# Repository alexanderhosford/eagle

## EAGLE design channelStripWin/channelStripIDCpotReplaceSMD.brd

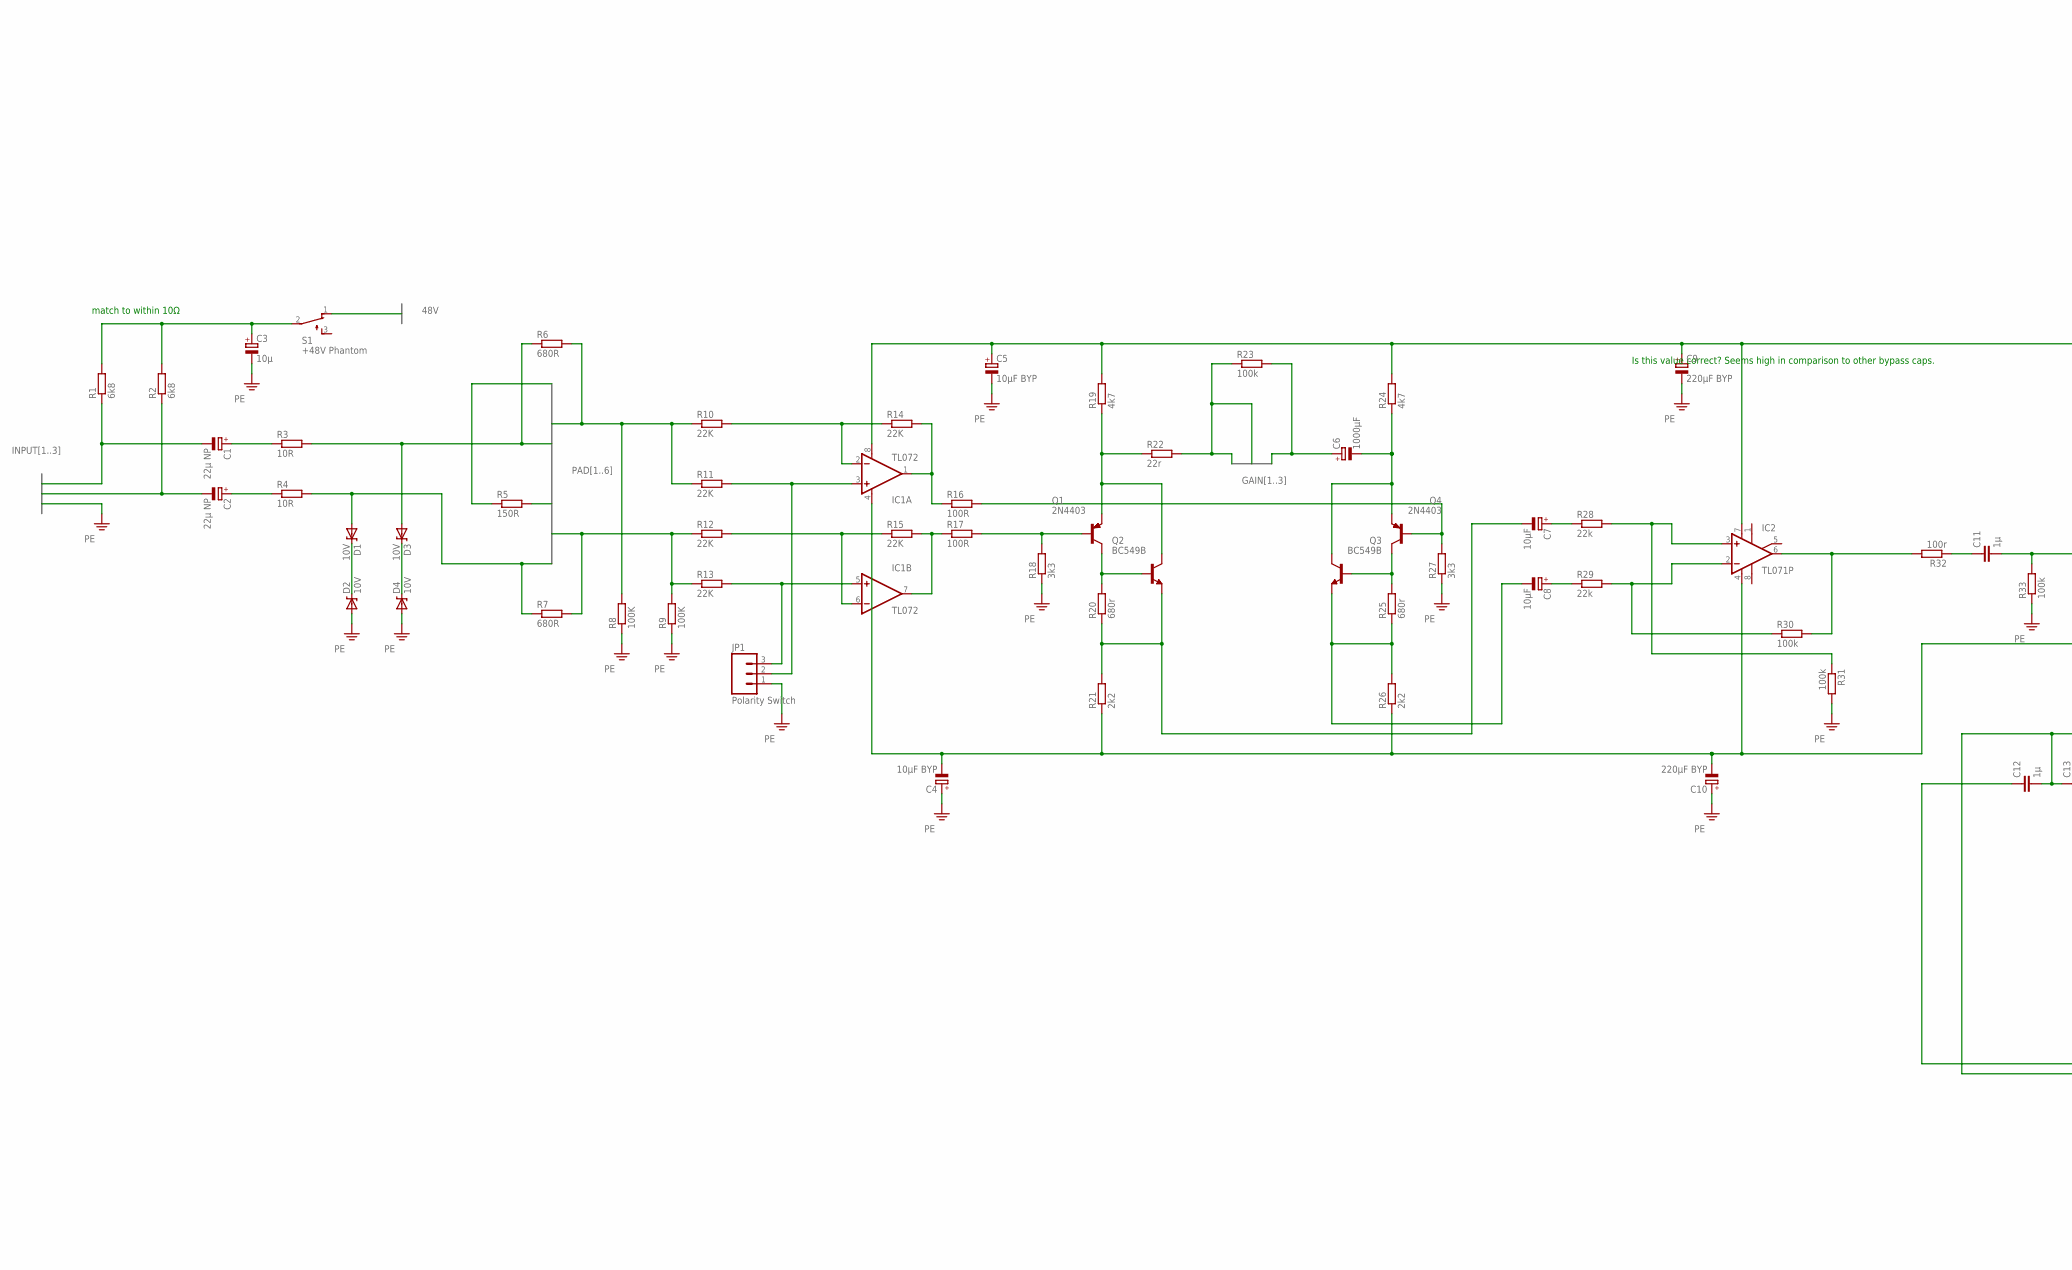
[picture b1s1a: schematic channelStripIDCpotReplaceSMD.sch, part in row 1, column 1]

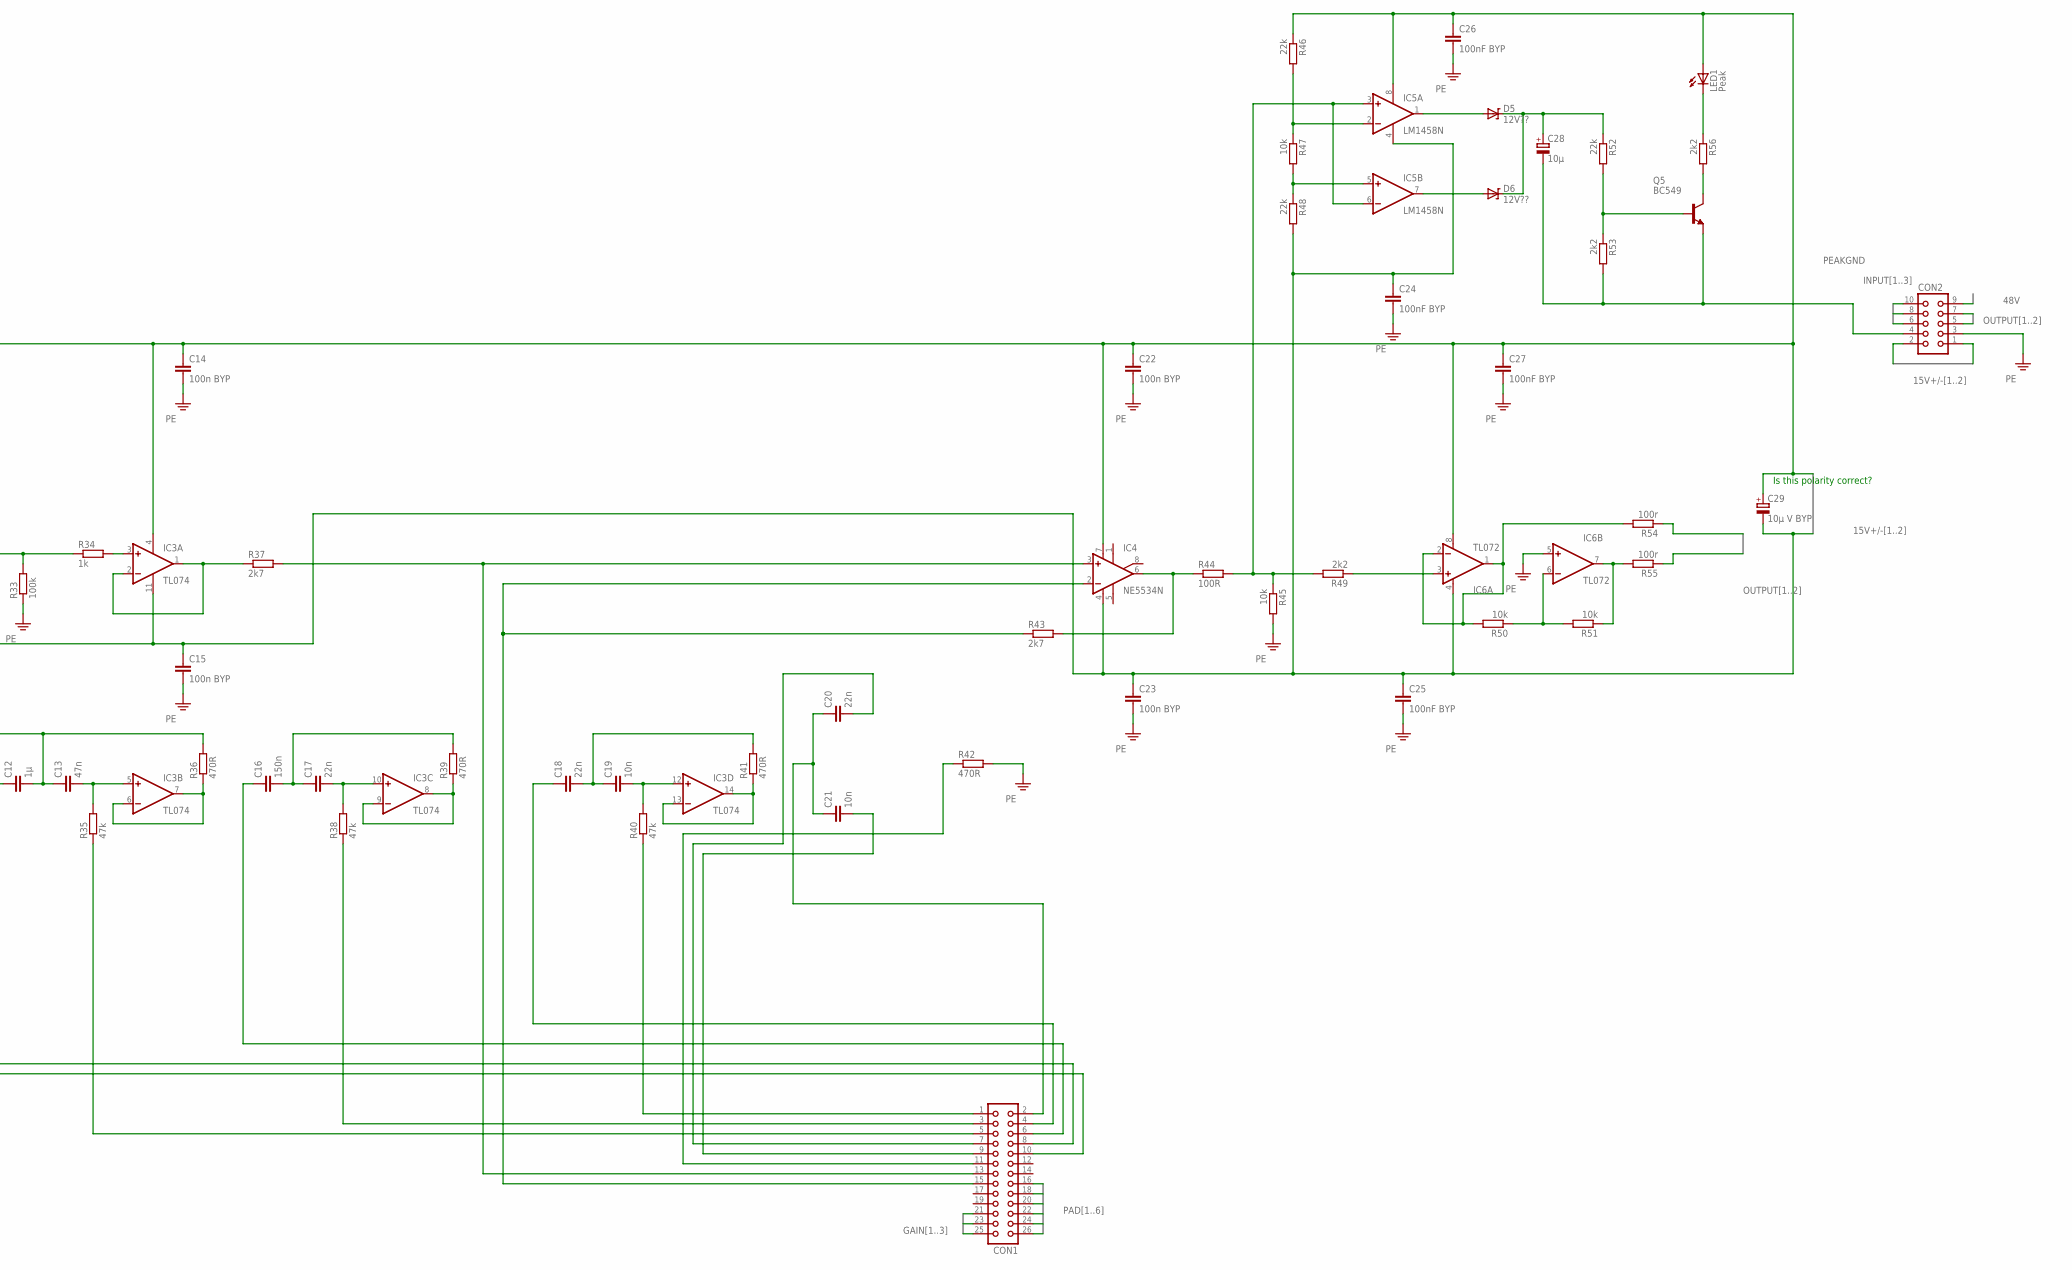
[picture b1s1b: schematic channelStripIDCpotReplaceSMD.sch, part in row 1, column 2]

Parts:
C1, C2: 22µ NP; E2,5-5
C3: 10µ; E2,5-6
C4, C5: 10µF BYP; E2,5-6
C6: 1000µF; E5-10,5
C7, C8: 10µF; E15-5
C9, C10: 220µF BYP; E5-10,5
C11, C12: 1µ; C050-025X075
C13: 47n; C050-025X075
C14, C15, C22, C23: 100n BYP; C050-025X075
C16: 150n; C050-025X075
C17, C18, C20: 22n; C050-025X075
C19, C21: 10n; C050-025X075
C24, C25, C26, C27: 100nF BYP; C050-025X075
C28: 10µ; E2,5-6E
C29: 10µ V BYP; E2,5-6E
CON1: CON26
CON2: CON10
D1, D2, D3, D4: 10V; DIODE-ZENER
D5, D6: 12V??; DIODE-ZENER
IC1, IC6: TL072; DIP08
IC2: TL071P; DIL08
IC3: TL074; DIL14
IC4: NE5534N; DIL08
IC5: LM1458N; DIL08
JP1: Polarity Switch; 1X03
LED1: Peak; LED3MM-NS
Q1, Q4: 2N4403; TO92-BCE
Q2, Q3: BC549B; TO92-EBC
Q5: BC549; TO92-EBC
R1, R2: 6k8; M1206
R3, R4: 10R; M1206
R5: 150R; M1206
R6, R7: 680R; M1206
R8, R9: 100K; M1206
R10, R11, R12, R13, R14, R15: 22K; M1206
R16, R17, R44: 100R; M1206
R18, R27: 3k3; M1206
R19, R24: 4k7; M1206
R20, R25: 680r; M1206
R21, R26, R49, R53, R56: 2k2; M1206
R22: 22r; M1206
R23, R30, R31, R33: 100k; M1206
R28, R29, R46, R48, R52: 22k; M1206
R32, R54, R55: 100r; M1206
R34: 1k; M1206
R35, R38, R40: 47k; M1206
R36, R39, R41, R42: 470R; M1206
R37, R43: 2k7; M1206
R45, R47, R50, R51: 10k; M1206
S1: +48V Phantom; TL3XPO

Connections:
15V+/-1: C4.-, C10.-, C15.1, C23.1, C24.1, C25.1, C29.-, CON2.1, IC1.4 (V-), IC2.4 (V-), IC3.11 (V-), IC4.4 (V-), IC5.4 (V-), IC6.4 (V-), R21.1, R26.1, R48.2
15V+/-2: C5.+, C9.+, C14.1, C22.1, C26.1, C27.1, C29.+, CON2.2, IC1.8 (V+), IC2.7 (V+), IC3.4 (V+), IC4.7 (V+), IC5.8 (V+), IC6.8 (V+), LED1.A, R19.2, R24.2, R46.1
48V: CON2.9, S1.1 (O)
GAIN1: C6.+, CON1.21, R23.2
GAIN2: CON1.23, CON1.25, R22.2, R23.1
GND: C3.-, C4.+, C5.-, C9.-, C10.+, C14.2, C15.2, C22.2, C23.2, C24.2, C25.2, C26.2, C27.2, D2.P$2 (A), D4.P$2 (A), IC6.5 (+IN), JP1.1, R8.1, R9.1, R18.1, R27.1, R31.2, R33.1, R42.2, R45.2
INPUT1: C1.-, CON2.10, R1.1
INPUT2: C2.-, CON2.8, R2.1
INPUT3: CON2.6
unnamed: C18.1, CON1.4
unnamed: IC6.7 (OUT), R51.1, R55.2
unnamed: C7.-, Q2.E, R20.1, R21.2
unnamed: C16.2, C17.1, R39.2
unnamed: C18.2, C19.1, R41.2
unnamed: C21.2, CON1.9
unnamed: C20.2, CON1.7
unnamed: CON1.11, R42.1
unnamed: IC3.13 (-IN), IC3.14 (OUT), R41.1
unnamed: C19.2, IC3.12 (+IN), R40.2
unnamed: CON1.3, R38.1
unnamed: C11.1, R32.1
unnamed: C11.2, R33.2, R34.1
unnamed: IC3.3 (+IN), R34.2
unnamed: IC3.1 (OUT), IC3.2 (-IN), R37.1
unnamed: CON1.15, IC4.2 (-IN), R43.1
unnamed: IC4.6 (OUT), R43.2, R44.1
unnamed: Q5.B, R52.2, R53.1
unnamed: C1.+, R3.1
unnamed: IC3.6 (-IN), IC3.7 (OUT), R36.1
unnamed: C13.2, IC3.5 (+IN), R35.2
unnamed: CON1.5, R35.1
unnamed: C12.1, CON1.8
unnamed: IC3.8 (OUT), IC3.9 (-IN), R39.1
unnamed: C2.+, R4.1
unnamed: C17.2, IC3.10 (+IN), R38.2
unnamed: CON1.1, R40.1
unnamed: IC5.2 (-IN), R46.2, R47.1
unnamed: C3.+, R1.2, R2.2, S1.2
unnamed: IC2.3 (+IN), R28.2, R31.1
unnamed: IC6.6 (-IN), R50.1, R51.2
unnamed: IC6.1 (OUT), IC6.2 (-IN), R50.2, R54.2
unnamed: IC6.3 (+IN), R49.1
unnamed: C20.1, C21.1, CON1.2
unnamed: C7.+, R28.1
unnamed: IC2.6 (OUT), R30.2, R32.2
unnamed: IC2.2 (-IN), R29.2, R30.1
unnamed: C8.+, R29.1
unnamed: C6.-, Q3.C, Q4.E, R24.1
unnamed: Q1.E, Q2.C, R19.1, R22.1
unnamed: Q3.B, Q4.C, R25.2
unnamed: IC1.1 (OUT), R14.2, R16.1
unnamed: Q1.C, Q2.B, R20.2
unnamed: IC5.5 (+IN), R47.2, R48.1
unnamed: IC1.7 (OUT), R15.2, R17.1
unnamed: C8.-, Q3.E, R25.1, R26.2
unnamed: Q4.B, R16.2, R27.2
unnamed: Q1.B, R17.2, R18.2
unnamed: IC1.6 (-IN), R12.2, R15.1
unnamed: D3.P$1 (C), D4.P$1 (C)
unnamed: IC1.2 (-IN), R10.2, R14.1
unnamed: IC1.5 (+IN), JP1.3, R13.2
unnamed: IC1.3 (+IN), JP1.2, R11.2
unnamed: D1.P$1 (C), D2.P$1 (C)
unnamed: Q5.C, R56.2
unnamed: C28.+, D5.P$1 (C), D6.P$1 (C), R52.1
unnamed: LED1.K (C), R56.1
unnamed: D5.P$2 (A), IC5.1 (OUT)
unnamed: D6.P$2 (A), IC5.7 (OUT)
unnamed: IC5.3 (+IN), IC5.6 (-IN), R44.2, R45.1, R49.2
unnamed: CON1.13, IC4.3 (+IN), R37.2
unnamed: C16.1, CON1.6
unnamed: C12.2, C13.1, CON1.10, R36.2
OUTPUT1: CON2.5, R55.1
OUTPUT2: CON2.7, R54.1
PAD1: CON1.16, R5.1
PAD2: CON1.18, R6.2, R8.2, R10.1, R11.1
PAD3: CON1.20, D3.P$2 (A), R3.2, R6.1
PAD4: CON1.22, R5.2
PAD5: CON1.24, R7.2, R9.2, R12.1, R13.1
PAD6: CON1.26, D1.P$2 (A), R4.2, R7.1
PE: CON2.3
PEAKGND: C28.-, CON2.4, Q5.E, R53.2

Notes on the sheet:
Is this polarity correct?
Is this value correct? Seems high in comparison to other bypass caps.
match to within 10Ω

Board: 2 copper layers, 107 parts (0 on the bottom side), 80 nets, no tracks yet.

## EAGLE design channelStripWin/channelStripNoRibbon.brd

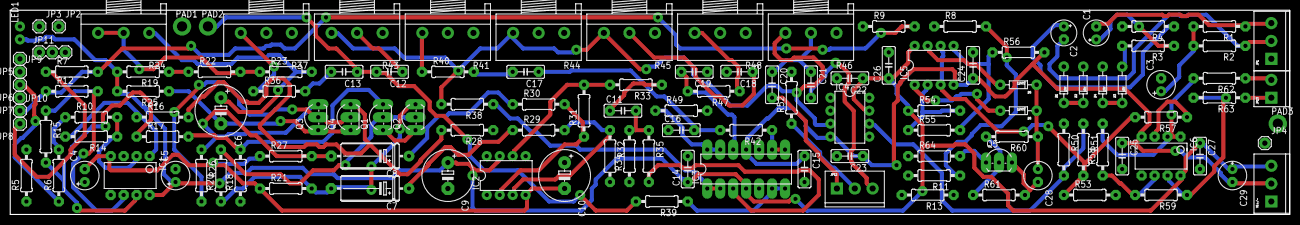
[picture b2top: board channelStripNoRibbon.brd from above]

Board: 2 copper layers, 250.6 x 40.0 mm, 128 parts (0 on the bottom side), 80 nets.

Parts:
C1, C2: 22µ NP; E2,5-5
C3: 10µ; E2,5-6
C4, C5: 10µF BYP; E2,5-6
C6: 1000µF; E5-10,5
C7, C8: 10µF; E15-5
C9, C10: 220µF BYP; E5-10,5
C11, C12: 1µ; C050-025X075
C13: 47n; C050-025X075
C14, C15, C22, C23: 100n BYP; C050-025X075
C16: 150n; C050-025X075
C17, C18, C20: 22n; C050-025X075
C19, C21: 10n; C050-025X075
C24, C25, C26, C27: 100nF BYP; C050-025X075
C28: 10µ; E2,5-6E
C29: 10µ V BYP; E2,5-6E
D1, D2, D3, D4: 10V; DIODE-ZENER
D5, D6: 12V??; DIODE-ZENER
IC1, IC6: TL072; DIP08
IC2: TL071P; DIL08
IC3: TL074; DIL14
IC4: NE5534N; DIL08
IC5: LM1458N; DIL08
JP1: INPUT; SCREWTERMINAL-3.5MM-3
JP2: Phantom On to input; 1X01
JP3: Phantom on to power; 1X01
JP4: +48; 1X01
JP5: 20dB pad L off; 1X01
JP6: 20dB pad L on; 1X01
JP7, JP8: 20dB pad R off; 1X01
JP9: 20dB pad L; 1X01
JP10: 20dB pad R; 1X01
JP11: Polarity Switch; 1X03
JP12: Hi F; SCREWTERMINAL-3.5MM-3
JP13: OUTPUT; SCREWTERMINAL-3.5MM-2
LED1: Peak; LED3MM-NS
PAD1: Shelf/Peak Pin 2; 1X01_2MM
PAD2: Shelf/Peak Pin 1; 1X01_2MM
PAD3: Peak GND; 1X01_2MM
Q1, Q4: 2N4403; TO92-BCE
Q2, Q3: BC549B; TO92-EBC
Q5: BC549; TO92-EBC
R1, R2: 6k8; 0207/10
R3, R4: 10R; 0207/10
R5: 150R; 0207/10
R6, R7: 680R; 0207/10
R8, R9: 100K; 0207/10
R10, R11, R12, R13, R14, R15: 22K; 0207/10
R16, R17, R51: 100R; 0207/10
R18, R28: 3k3; 0207/10
R19, R25: 4k7; 0207/10
R20, R26: 680r; 0207/10
R21, R27, R57, R61, R64: 2k2; 0207/10
R22: 22r; 0207/10
R23, R31, R32, R34: 100k; 0207/10
R24, R43, R44, R45, R46: 10k; 3RP/1610N
R29, R30, R54, R56, R60: 22k; 0207/10
R33, R62, R63: 100r; 0207/10
R35: 1k; 0207/10
R36, R40, R47: 47k; 0207/10
R37, R41, R48: 1M; 3RP/1610N
R38, R50: 2k7; 0207/10
R39, R42, R49, R52: 470R; 0207/10
R53, R55, R58, R59: 10k; 0207/10
VE+/-: POWER; SCREWTERMINAL-3.5MM-3

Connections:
15V+: C5.+, C9.+, C14.1, C22.1, C26.1, C27.1, C29.+, IC1.8, IC2.7, IC3.4, IC4.7, IC5.8, IC6.8, LED1.A, R19.2, R25.2, R54.1, VE+/-.3
15V-: C4.-, C10.-, C15.1, C23.1, C24.1, C25.1, C29.-, IC1.4, IC2.4, IC3.11, IC4.4, IC5.4, IC6.4, R21.1, R27.1, R56.2, VE+/-.2
unnamed: C18.1, R45.2
unnamed: IC6.7, R59.1, R63.2
unnamed: C7.-, Q2.E, R20.1, R21.2
unnamed: C12.2, C13.1, PAD2.1, R39.2
unnamed: C16.2, C17.1, R42.2
unnamed: C18.2, C19.1, R49.2
unnamed: C21.2, JP12.3
unnamed: C20.2, JP12.1
unnamed: JP12.2, R52.1
unnamed: IC3.13, IC3.14, R49.1
unnamed: C19.2, IC3.12, R47.2
unnamed: R47.1, R48.3
unnamed: C11.1, R33.1
unnamed: C11.2, R34.2, R35.1
unnamed: IC3.3, R35.2
unnamed: IC3.1, IC3.2, R38.1
unnamed: IC4.2, R43.1, R44.1, R45.1, R46.1, R50.1
unnamed: IC4.6, R50.2, R51.1
unnamed: Q5.B, R60.2, R61.1
unnamed: C1.+, R3.1
unnamed: IC3.6, IC3.7, R39.1
unnamed: C13.2, IC3.5, R36.2
unnamed: R36.1, R37.3
unnamed: C12.1, PAD1.1, R43.2
unnamed: IC3.8, IC3.9, R42.1
unnamed: C2.+, R4.1
unnamed: C17.2, IC3.10, R40.2
unnamed: R40.1, R41.3
unnamed: IC5.2, R54.2, R55.1
unnamed: C1.-, JP1.3, R1.1
unnamed: C2.-, JP1.2, R2.1
unnamed: C3.+, JP2.1, R1.2, R2.2
unnamed: JP13.1, R63.1
unnamed: JP3.1, JP4.1
unnamed: JP10.1, R7.2, R9.2, R12.1, R13.1
unnamed: JP13.2, R62.1
unnamed: IC2.3, R29.2, R32.1
unnamed: IC6.6, R58.1, R59.2
unnamed: IC6.1, IC6.2, R58.2, R62.2
unnamed: IC6.3, R57.1
unnamed: C20.1, C21.1, R46.2
unnamed: C7.+, R29.1
unnamed: IC2.6, R31.2, R33.2
unnamed: IC2.2, R30.2, R31.1
unnamed: C8.+, R30.1
unnamed: R22.2, R23.1, R24.2, R24.3
unnamed: C6.+, R23.2, R24.1
unnamed: C6.-, Q3.C, Q4.E, R25.1
unnamed: Q1.E, Q2.C, R19.1, R22.1
unnamed: Q3.B, Q4.C, R26.2
unnamed: IC1.1, R14.2, R16.1
unnamed: Q1.C, Q2.B, R20.2
unnamed: IC5.5, R55.2, R56.1
unnamed: IC1.7, R15.2, R17.1
unnamed: C8.-, Q3.E, R26.1, R27.2
unnamed: Q4.B, R16.2, R28.2
unnamed: Q1.B, R17.2, R18.2
unnamed: IC1.6, R12.2, R15.1
unnamed: D3.P$1, D4.P$1
unnamed: IC1.2, R10.2, R14.1
unnamed: IC1.5, JP11.3, R13.2
unnamed: IC1.3, JP11.2, R11.2
unnamed: JP9.1, R6.2, R8.2, R10.1, R11.1
unnamed: D1.P$1, D2.P$1
unnamed: Q5.C, R64.2
unnamed: JP7.1, R5.2
unnamed: JP5.1, R5.1
unnamed: D1.P$2, JP8.1, R4.2, R7.1
unnamed: C28.+, D5.P$1, D6.P$1, R60.1
unnamed: LED1.K, R64.1
unnamed: D5.P$2, IC5.1
unnamed: D6.P$2, IC5.7
unnamed: D3.P$2, JP6.1, R3.2, R6.1
unnamed: IC5.3, IC5.6, R51.2, R53.1, R57.2
unnamed: IC4.3, R38.2, R43.3, R44.3, R45.3, R46.3
unnamed: C16.1, R44.2
PE: C3.-, C4.+, C5.-, C9.-, C10.+, C14.2, C15.2, C22.2, C23.2, C24.2, C25.2, C26.2, C27.2, D2.P$2, D4.P$2, IC6.5, JP1.1, JP11.1, R8.1, R9.1, R18.1, R28.1, R32.2, R34.1, R37.1, R37.2, R41.1, R41.2, R48.1, R48.2, R52.2, R53.2, VE+/-.1
PEAKGND: C28.-, PAD3.1, Q5.E, R61.2

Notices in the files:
parts and their libraries:
SparkFun: Licensing: CC v3.0 Share-Alike You are welcome to use this library for commercial purposes.
